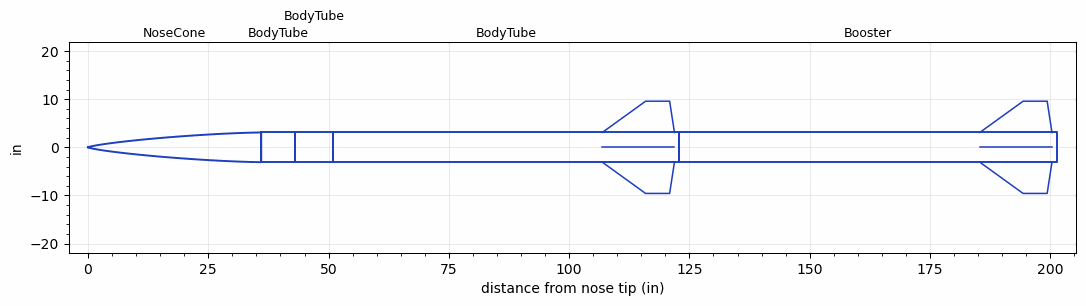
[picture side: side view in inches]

<RASAeroDocument>
 <FileVersion>2</FileVersion>
 <RocketDesign>
  <NoseCone>
   <Length>36</Length>
   <Diameter>6.17</Diameter>
   <Shape>Von Karman Ogive</Shape>
   <Location>0</Location>
  </NoseCone>
  <BodyTube>
   <Length>7.11</Length>
   <Diameter>6.17</Diameter>
   <Location>36</Location>
  </BodyTube>
  <BodyTube>
   <Length>7.78</Length>
   <Diameter>6.17</Diameter>
   <Location>43.11</Location>
  </BodyTube>
  <BodyTube>
   <Length>72</Length>
   <Diameter>6.17</Diameter>
   <Location>50.89</Location>
   <Fin>
    <Count>4</Count>
    <Chord>15</Chord>
    <Span>6.5</Span>
    <SweepDistance>9</SweepDistance>
    <TipChord>5</TipChord>
    <Thickness>0.5</Thickness>
    <LERadius>0.5</LERadius>
    <Location>16</Location>
    <AirfoilSection>Double Wedge</AirfoilSection>
    <FX1>1</FX1>
    <FX3>1</FX3>
   </Fin>
  </BodyTube>
  <Booster>
   <Length>78.468</Length>
   <Diameter>6.17</Diameter>
   <InsideDiameter>6.17</InsideDiameter>
   <Location>122.89</Location>
   <ShoulderLength>0</ShoulderLength>
   <Fin>
    <Count>4</Count>
    <Chord>15</Chord>
    <Span>6.5</Span>
    <SweepDistance>9</SweepDistance>
    <TipChord>5</TipChord>
    <Thickness>0.5</Thickness>
    <LERadius>0.5</LERadius>
    <Location>16</Location>
    <AirfoilSection>Double Wedge</AirfoilSection>
    <FX1>1</FX1>
    <FX3>1</FX3>
   </Fin>
  </Booster>
  <Surface>Smooth (Zero Roughness)</Surface>
  <ModifiedBarrowman>False</ModifiedBarrowman>
  <Turbulence>False</Turbulence>
  <UseBooster1>False</UseBooster1>
  <UseBooster2>False</UseBooster2>
 </RocketDesign>
 <LaunchSite>
  <Altitude>5000</Altitude>
  <Pressure>0</Pressure>
  <RodAngle>0</RodAngle>
  <RodLength>24</RodLength>
  <Temperature>90</Temperature>
  <WindSpeed>0</WindSpeed>
 </LaunchSite>
 <Recovery>
  <Altitude1>1000</Altitude1>
  <Altitude2>1000</Altitude2>
  <DeviceType1>Parachute</DeviceType1>
  <DeviceType2>None</DeviceType2>
  <Event1>True</Event1>
  <Event2>False</Event2>
  <Size1>48</Size1>
  <Size2>1</Size2>
  <EventType1>Apogee</EventType1>
  <EventType2>None</EventType2>
  <CD1>0.97</CD1>
  <CD2>1.33</CD2>
 </Recovery>
 <SimulationList>
  <Simulation>
   <SustainerEngine>TCIMC3_(9899.7771)_5_5_2.329_11.0789_2  (GTXR)</SustainerEngine>
   <SustainerLaunchWt>113.29</SustainerLaunchWt>
   <SustainerNozzleDiameter>4.46</SustainerNozzleDiameter>
   <SustainerCG>76.38</SustainerCG>
   <SustainerIgnitionDelay>20</SustainerIgnitionDelay>
   <Booster1Engine>TCIMC3_(9899.7771)_5_5_2.329_11.0789_2  (GTXR)</Booster1Engine>
   <Booster1LaunchWt>213.38</Booster1LaunchWt>
   <Booster1SeparationDelay>2</Booster1SeparationDelay>
   <Booster1IgnitionDelay>0</Booster1IgnitionDelay>
   <Booster1CG>112.35</Booster1CG>
   <Booster1NozzleDiameter>4.46</Booster1NozzleDiameter>
   <IncludeBooster1>True</IncludeBooster1>
   <Booster2Delay>0</Booster2Delay>
   <IncludeBooster2>False</IncludeBooster2>
   <TimetoApogee>125.9465</TimetoApogee>
   <MaxAltitude>168027.5</MaxAltitude>
   <MaxVelocity>3741.659</MaxVelocity>
   <OptimumWt>81.57834</OptimumWt>
   <OptimumMaxAlt>81.57834</OptimumMaxAlt>
  </Simulation>
 </SimulationList>
</RASAeroDocument>
